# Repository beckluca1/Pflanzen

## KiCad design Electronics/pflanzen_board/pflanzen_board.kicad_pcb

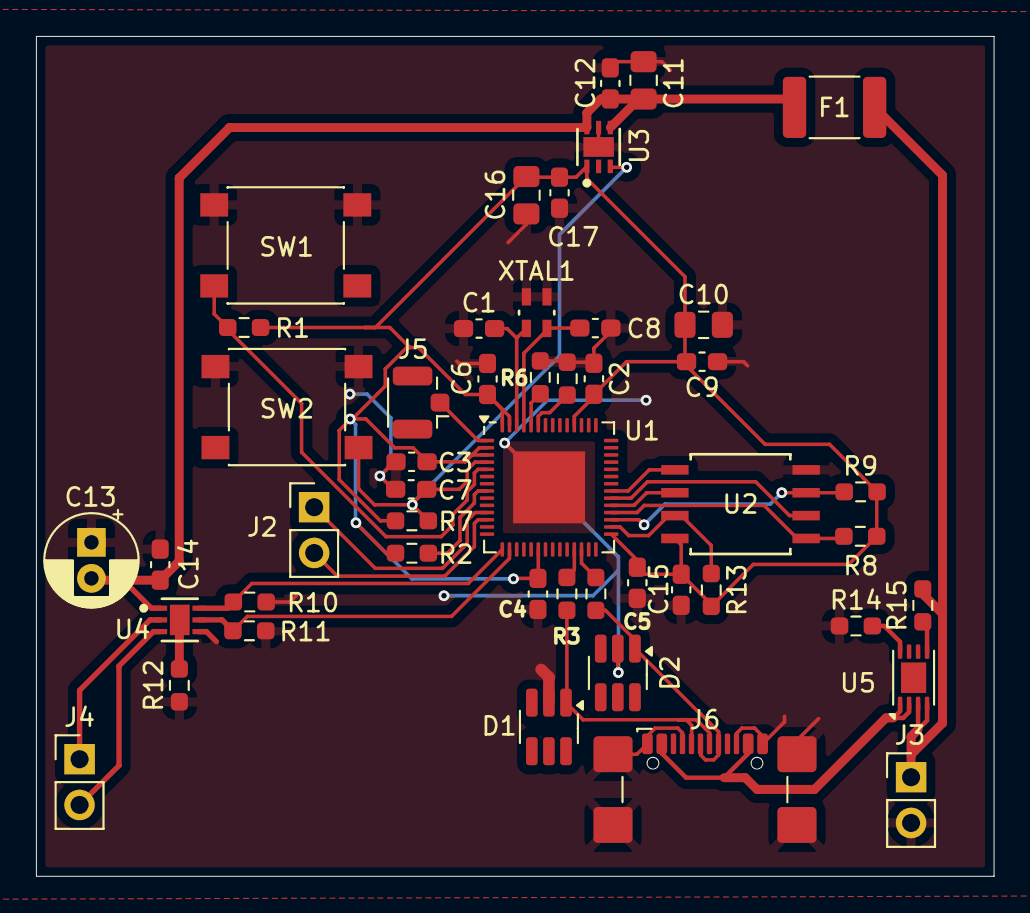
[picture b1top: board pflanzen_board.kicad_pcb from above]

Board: 2 copper layers, 53.2 x 46.7 mm, 48 parts (0 on the bottom side), 32 nets.

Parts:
C1, C8: 10pF; C_0603_1608Metric_Pad1.08x0.95mm_HandSolder
C2, C3, C4, C5, C6, C7, C12, C14, C15, C17: 0.1µF; C_0603_1608Metric_Pad1.08x0.95mm_HandSolder
C9: 1µF; C_0603_1608Metric_Pad1.08x0.95mm_HandSolder
C10, C11, C16: 10µF; C_0805_2012Metric_Pad1.18x1.45mm_HandSolder
C13: 220µF; CP_Radial_D5.0mm_P2.00mm
D1, D2: D_TVS; SOT-23-6_Handsoldering
F1: Polyfuse; Fuse_1812_4532Metric_Pad1.30x3.40mm_HandSolder
J2, J3, J4: Conn_01x02_Pin; PinHeader_1x02_P2.54mm_Vertical
J5: Conn_Coaxial; U.FL_Hirose_U.FL-R-SMT-1_Vertical
J6: UJ20-C-H-G-SMT-1-P16-TR; USB_C_Receptacle_GCT_USB4110_Edit
R1, R2, R5, R6, R7, R8, R9, R10, R11, R12, R13: 10kΩ; R_0603_1608Metric_Pad0.98x0.95mm_HandSolder
R3, R4: 22Ω; R_0603_1608Metric_Pad0.98x0.95mm_HandSolder
R14: 1kΩ; R_0603_1608Metric_Pad0.98x0.95mm_HandSolder
R15: 620Ω; R_0603_1608Metric_Pad0.98x0.95mm_HandSolder
SW1, SW2: SW_SPST; SW_Push_1P1T_NO_6x6mm_H9.5mm
U1: ESP32-S3; QFN-56-1EP_7x7mm_P0.4mm_EP4x4mm
U2: W25Q64JVSSIQ; SOIC-8_5P28X5P28_WIN
U3: TPS7A2501DRVR; DRV0006A-IPC_A
U4: DRV8210DSGR; DRV0006A-IPC_A
U5: MCP73831-5-MC; DFN-8-1EP_3x2mm_P0.5mm_EP1.7x1.4mm
XTAL1: NX2016SA-40M-STD-CZS-3; NX2016SA-40M-STD-CZS-3_NDK

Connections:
3.3V: C2.2, C3.2, C4.2, C5.2, C6.2, C9.2, C10.2, C15.2, C16.2, C17.2, R1.2, R2.2, R7.2, R8.2, R9.2, R13.2, U1.2 (VDD3P3), U1.3 (VDD3P3), U1.20 (VDD3P3_RTC), U1.29 (VDD_SPI), U1.46 (VDD3P3_CPU), U1.55 (VDDA), U1.56 (VDDA), U2.8 (VCC), U3.1 (OUT)
ANT: J5.1 (In), U1.1 (LNA_IN)
Button_1: J2.1, U1.11 (GPIO6)
Button_2: J2.2, U1.12 (GPIO7)
CLK: U1.33 (SPICLK), U2.6 (CLK)
CS: R8.1, U1.32 (SPICS0), U2.1 (/CS)
D+: D2.1 (A1), J6.A6 (DP1), J6.B6 (DP2), R4.2
D-: D1.1 (A1), J6.A7 (DN1), J6.B7 (DN2), R3.2
DI: U1.35 (SPID), U2.5 (DI(IO0))
DO: U1.34 (SPIQ), U2.2 (DO(IO1))
GND: C1.1, C2.1, C3.1, C4.1, C5.1, C6.1, C7.2, C8.1, C9.1, C10.1, C11.1, C12.1, C13.1, C14.1, C15.1, C16.1, C17.1, D1.2 (A2), D2.2 (A2), J3.2, J6.A1_B12 (GND), J6.A5 (CC1), J6.A12_B1 (GND__1), J6.B5 (CC2), J6.SH1 (SHIELD), J6.SH2 (SHIELD__1), J6.SH3 (SHIELD__2), J6.SH4 (SHIELD__3), R5.2, R6.2, R10.1, R11.1, R12.1, R14.1, SW1.2 (B), SW2.2 (B), U1.57 (GND), U2.4 (GND), U3.5 (GND), U3.7 (Thermal_Pad), U4.4 (GND), U5.6 (V_{SS}), XTAL1.2, XTAL1.3
HD: R13.1, U1.30 (SPIHD), U2.7 (/HOLD_OR_/RESET(IO3))
MS_1: R10.2, U1.15 (GPIO10), U4.6 (IN1_PH)
MS_2: R11.2, U1.16 (GPIO11), U4.5 (IN2_EN)
Motor_1: J4.1, U4.2 (OUT1)
Motor_2: J4.2, U4.3 (OUT2)
unnamed: R1.1, SW1.1 (A), U1.5 (GPIO0)
unnamed: R2.1, U1.8 (GPIO3)
unnamed: R3.1, U1.25 (GPIO19/USB_D-)
unnamed: R4.1, U1.26 (GPIO20/USB_D+)
unnamed: R5.1, U1.51 (GPIO45)
unnamed: R6.1, U1.52 (GPIO46)
unnamed: R12.2, U4.7 (MODE)
unnamed: R14.2, U5.8 (PROG)
unnamed: R15.1, U5.5 (STAT)
PU: C7.1, R7.1, SW2.1 (A), U1.4 (CHIP_PU), U3.3 (PG)
VBAT: F1.1, J3.1, R15.2, U5.3 (V_{BAT}), U5.4 (V_{BAT})
VBUS: J6.A4_B9 (VBUS), J6.A9_B4 (VBUS__1), U5.1 (V_{DD}), U5.2 (V_{DD})
VCC: C11.2, C12.2, C13.2, C14.2, F1.2, U3.4 (EN), U3.6 (IN), U4.1 (VM)
WP: R9.1, U1.31 (SPIWP), U2.3 (/WP(IO2))
XN: C8.2, U1.53 (XTAL_N), XTAL1.1
XP: C1.2, U1.54 (XTAL_P), XTAL1.4

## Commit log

2026-04-14 Handle server not responding
2026-04-17 feat: Upload hardware & electronics
2026-05-06 feat: update electronics
2026-05-06 feat: upload seperate website file
2026-05-06 feat: webserver downloads website
2026-05-06 feat: settings on website
2026-05-06 fix: update only on boot
2026-05-06 fix: more stable file download
2026-05-09 feat: secure download
2026-05-09 fix: renamed script key file
2026-05-09 fix: removed old script key file
2026-05-09 fix: renamed folder
2026-05-11 feat: init phase for wifi setup
2026-05-11 fix: update index hmac
2026-05-11 fix: update style hmac
2026-05-11 fix: update script hmac
2026-05-11 fix: get correct credentials
2026-05-11 fix: updated hmacs
2026-05-11 fix: credentials
2026-05-11 fix: script hmac
2026-05-11 feat: use ed25519 for signing
2026-05-11 fix: new secret keys
2026-05-11 fix: python hashing
2026-05-11 fix: compatible signatures
2026-05-11 fix: remove debug
